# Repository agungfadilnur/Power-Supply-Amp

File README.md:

## Power Supply for High Amplifier

Made By

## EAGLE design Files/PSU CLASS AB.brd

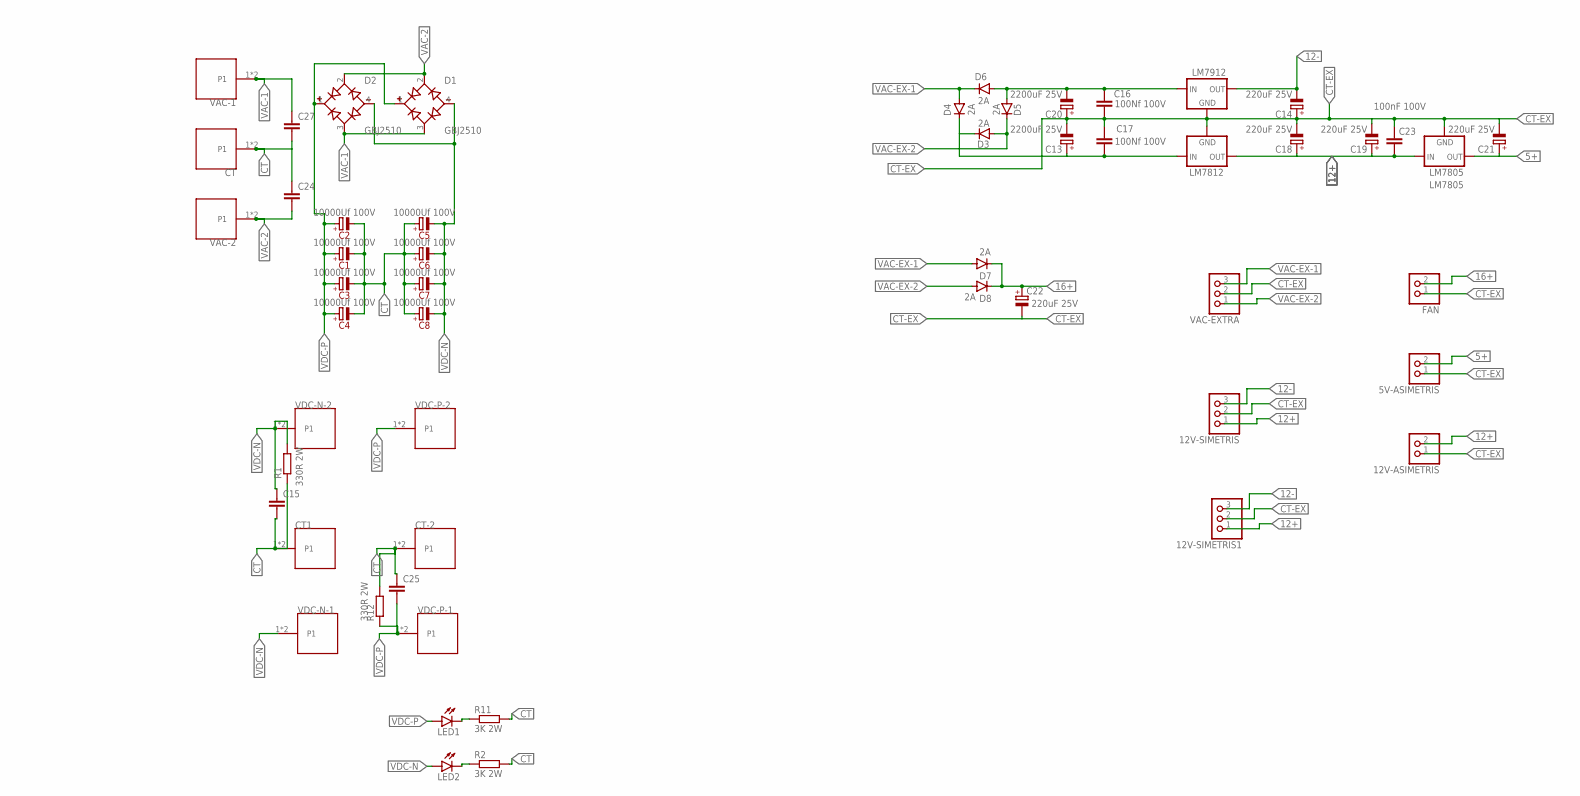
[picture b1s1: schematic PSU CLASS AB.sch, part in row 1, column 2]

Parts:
5V-ASIMETRIS, 12V-ASIMETRIS: PINHD-1X2; 1X02
12V-SIMETRIS, 12V-SIMETRIS1: PINHD-1X3; 1X03
C1, C2, C3, C4, C5, C6, C7, C8: 10000Uf 100V; E1,5-4
C13, C20: 2200uF 25V; E3,5-8
C14, C18, C19, C21, C22: 220uF 25V; E3,5-8
C15, C24, C25, C27: C10/5; C10B5
C16, C17: 100Nf 100V; C5B3
C23: 100nF 100V; C5B3
CT, CT1: 62409-1; TE_62409-1
CT-2: 62409-1; TE_62409-1
D1, D2: GBJ2510; DIOB_GBJ2510
D3, D4, D5, D6, D7, D8: 2A; DO41-10
FAN: PINHD-1X2; 1X02
H2: MOUNT-HOLE2.8; 2,8
LED1, LED2: LED3MM
LM7805: LM7805; 78XXS
LM7812: LM7812; 78XXS
LM7912: LM7912; 79XXS
R1, R12: 330R 2W; 0207/15
R2, R11: 3K 2W; 0207/15
VAC-1, VAC-2: 62409-1; TE_62409-1
VAC-EXTRA: PINHD-1X3; 1X03
VDC-N-1, VDC-N-2: 62409-1; TE_62409-1
VDC-P-1, VDC-P-2: 62409-1; TE_62409-1

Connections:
5+: 5V-ASIMETRIS.2, C21.+, LM7805.OUT
12+: 12V-ASIMETRIS.2, 12V-SIMETRIS.1, 12V-SIMETRIS1.1, C18.+, C19.+, C23.1, LM7805.IN, LM7812.OUT
12-: 12V-SIMETRIS.3, 12V-SIMETRIS1.3, C14.-, LM7912.OUT
16+: C22.+, D7.C, D8.C, FAN.2
CT: C1.-, C2.-, C3.-, C4.-, C5.+, C6.+, C7.+, C8.+, C15.2, C24.1, C25.1, C27.2, CT.1, CT.2, CT1.1, CT1.2, CT-2.1, CT-2.2, R1.1, R2.2, R11.2, R12.2
CT-EX: 5V-ASIMETRIS.1, 12V-ASIMETRIS.1, 12V-SIMETRIS.2, 12V-SIMETRIS1.2, C13.-, C14.+, C16.1, C17.2, C18.-, C19.-, C20.+, C21.-, C22.-, C23.2, FAN.1, LM7805.GND, LM7812.GND, LM7912.GND, VAC-EXTRA.2
unnamed: LED2.K (C), R2.1
unnamed: LED1.K (C), R11.1
unnamed: C16.2, C20.-, D5.A, D6.A, LM7912.IN
unnamed: C13.+, C17.1, D3.C, D4.C, LM7812.IN
VAC-1: C27.1, D1.3 (AC2), D2.3 (AC2), VAC-1.1, VAC-1.2
VAC-2: C24.2, D1.2 (AC1), D2.2 (AC1), VAC-2.1, VAC-2.2
VAC-EX-1: D4.A, D6.C, D7.A, VAC-EXTRA.3
VAC-EX-2: D3.A, D5.C, D8.A, VAC-EXTRA.1
VDC-N: C5.-, C6.-, C7.-, C8.-, C15.1, D1.4 (-), D2.4 (-), LED2.A, R1.2, VDC-N-1.1, VDC-N-1.2, VDC-N-2.1, VDC-N-2.2
VDC-P: C1.+, C2.+, C3.+, C4.+, C25.2, D1.1 (+), D2.1 (+), LED1.A, R12.1, VDC-P-1.1, VDC-P-1.2, VDC-P-2.1, VDC-P-2.2

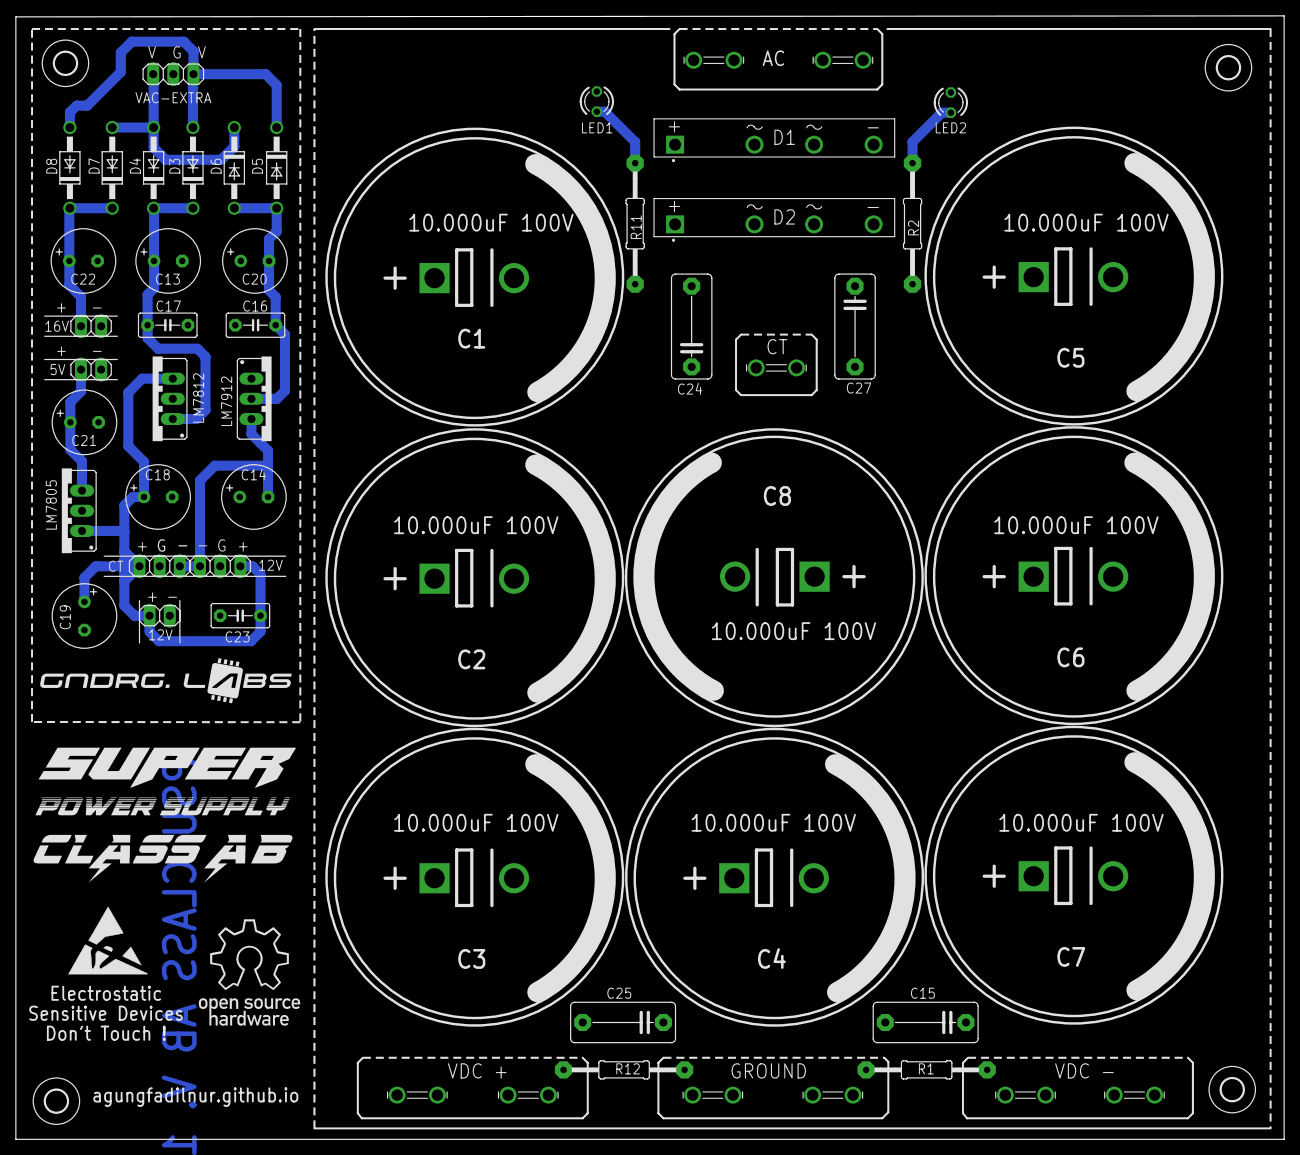
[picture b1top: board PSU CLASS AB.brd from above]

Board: 2 copper layers, 159.7 x 141.5 mm, 60 parts (0 on the bottom side), 16 nets.

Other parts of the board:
H1, H3, H4: MOUNT-HOLE2.8; 2,8
U$1: ESD_10.00
U$5: OPEN-HARDWARE
